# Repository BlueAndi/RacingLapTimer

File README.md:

# Racing Lap Timer
A racing lap timer, based on a laser sensor.

- [Racing Lap Timer](#racing-lap-timer)
- [Motivation](#motivation)
- [Initial Startup](#initial-startup)
- [Electronic](#electronic)
  - [Schematic](#schematic)
- [Software](#software)
  - [Preparation](#preparation)
  - [IDE](#ide)
  - [Installation](#installation)
  - [Build Project](#build-project)
  - [Update of the device](#update-of-the-device)
    - [Update via usb](#update-via-usb)
  - [Used Libraries](#used-libraries)
  - [System Context](#system-context)
- [Issues, Ideas And Bugs](#issues-ideas-and-bugs)
- [License](#license)
  - [Contribution](#contribution)

# Motivation
For line follower competitions a racing lap timer shall be used. It doesn't only measure the lap time, it shows it nice via web interface, inclusive automatically result table generation.

# Initial Startup
If the system starts up the first time, it will spawn a wifi access point with the SSID RacingLapTimer. Connect to it, it will request a password (default: "let me in").
Configure there the wifi network SSID/password to which the system shall later connect.

After configuration, the system will try to establish a connection. If the connection is not successful, the access point will be spawned again. Otherwise the credentials will be stored to persistent memory and loaded the next time automatically.

# Electronic

* [Wemos D1 Mini (esp8266)](https://docs.platformio.org/en/latest/boards/espressif8266/d1_mini.html)
* [Waveshare laser sensor](https://www.waveshare.com/wiki/Laser_Sensor)

## Schematic

Schematic files can be found [here](./doc/electronic/RacingLapTimer). These have been developed using KiCAD 6.

### MCU

- Digital signal of laser sensor is connected to D1/GPIO_5 of the Wemos D1 Mini.
- Power is supplied by USB 5V directly to the Wemos D1 Mini

### Laser Power Supply

- Laser module Vcc shall be 3.3V, because MCU is only 3.3V tolerant.
- THT or SMD resistor options are provided. **DO NOT PLACE ALL RESISTORS**.

### Laser Sensor

- Pin header for Waveshare Laser Sensor.

## PCB 
### v1.0

- It is recommended to give the Laser Sensor some kind of support in order to protect the pin header from breaking. The height of the support depends on the pin headers used.

# Software

## Preparation
Install the serial driver for the Wemos D1 Mini board. Find the latest drivers here: https://www.wemos.cc/en/latest/ch340_driver.html

## IDE
The [PlatformIO IDE](https://platformio.org/platformio-ide) is used for the development. Its build on top of Microsoft Visual Studio Code.

## Installation
1. Install [VSCode](https://code.visualstudio.com/).
2. Install PlatformIO IDE according to this [HowTo](https://platformio.org/install/ide?install=vscode).
3. Close and start VSCode again.
4. Recommended is to take a look to the [quick-start guide](https://docs.platformio.org/en/latest/ide/vscode.html#quick-start).

## Build Project
1. Load workspace in VSCode.
2. Change to PlatformIO toolbar.
3. _Project Tasks -> Build_ or via hotkey ctrl-alt-b

## Update of the device

### Update via usb
1. Connect the Wemos D1 Mini board to your PC via USB.
2. Build and upload the software via _Project Tasks -> Upload_.
3. Build and upload the filesystem via _Project Tasks -> Upload File System image_.

## Used Libraries
* [Arduino](https://github.com/esp8266/Arduino) - ESP framework.
* [WifiManager](https://github.com/tzapu/WiFiManager) - ESP8266 WiFi Connection manager with fallback web configuration portal.
* [WebSockets](https://github.com/Links2004/arduinoWebSockets) - A WebSocket Server and Client for Arduino based on RFC6455.

## System Context

# Issues, Ideas And Bugs
If you have further ideas or you found some bugs, great! Create a [issue](https://github.com/BlueAndi/RacingLapTimer/issues) or if you are able and willing to fix it by yourself, clone the repository and create a pull request.

# License
The whole source code is published under the [MIT license](http://choosealicense.com/licenses/mit/).

## Contribution
Unless you explicitly state otherwise, any contribution intentionally submitted for inclusion in the work by you, shall be licensed as above, without any
additional terms or conditions.

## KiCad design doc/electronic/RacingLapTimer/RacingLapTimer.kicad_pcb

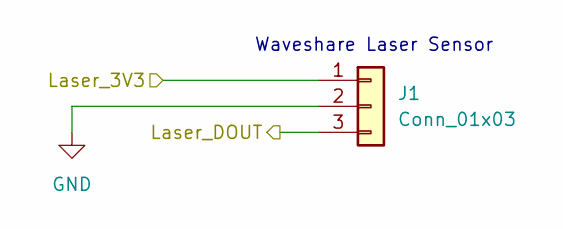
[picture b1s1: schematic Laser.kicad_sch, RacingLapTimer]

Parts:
J1: Conn_01x03; PinHeader_1x03_P2.54mm_Vertical

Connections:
/Laser/Laser_3V3: J1.1; also elsewhere on the board
/Laser/Laser_DOUT: J1.3; also elsewhere on the board
GND: J1.2; also elsewhere on the board

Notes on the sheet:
Waveshare Laser Sensor

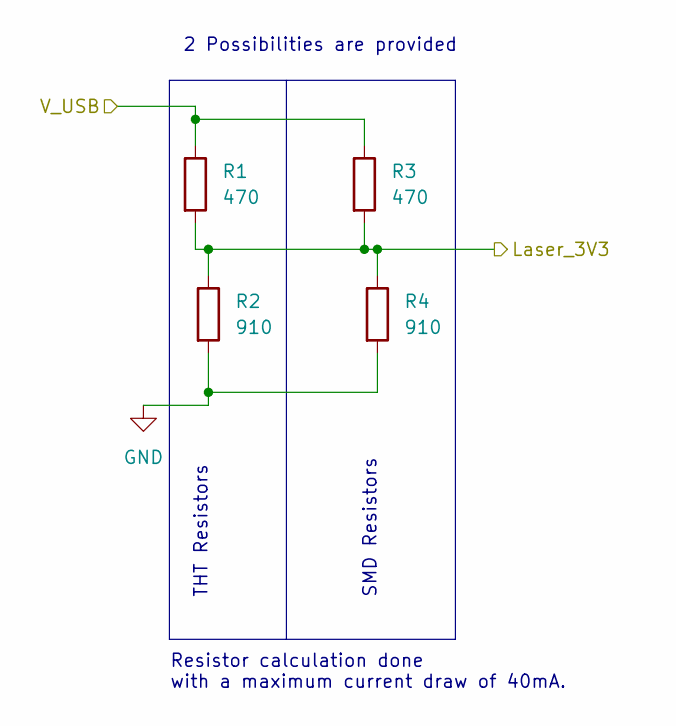
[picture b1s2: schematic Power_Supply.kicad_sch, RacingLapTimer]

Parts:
R1: 470; R_Axial_DIN0411_L9.9mm_D3.6mm_P15.24mm_Horizontal
R2: 910; R_Axial_DIN0411_L9.9mm_D3.6mm_P15.24mm_Horizontal
R3: 470; R_1206_3216Metric
R4: 910; R_1206_3216Metric

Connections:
/Laser/Laser_3V3: R1.2, R2.1, R3.2, R4.1; also elsewhere on the board
/MCU/V_USB: R1.1, R3.1; also elsewhere on the board
GND: R2.2, R4.2; also elsewhere on the board

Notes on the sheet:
SMD Resistors
2 Possibilities are provided
THT Resistors
Resistor calculation done with a maximum current draw of 40mA.

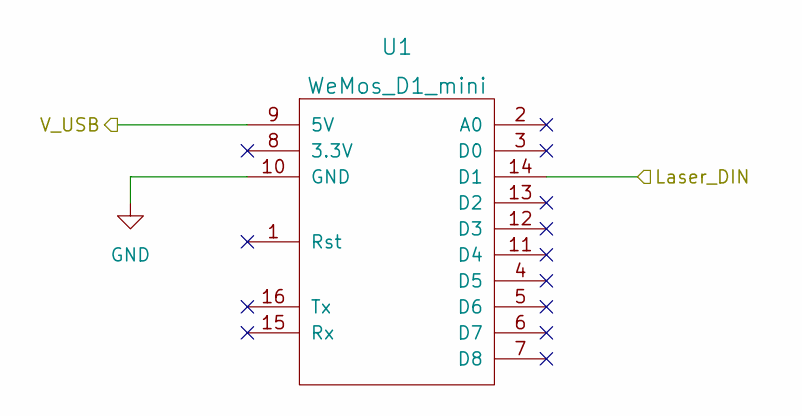
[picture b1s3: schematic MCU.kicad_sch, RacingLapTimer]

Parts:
U1: WeMos_D1_mini; wemos-d1-mini-with-pin-header-and-connector

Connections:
/Laser/Laser_DOUT: U1.14 (D1); also elsewhere on the board
/MCU/V_USB: U1.9 (5V); also elsewhere on the board
GND: U1.10 (GND); also elsewhere on the board

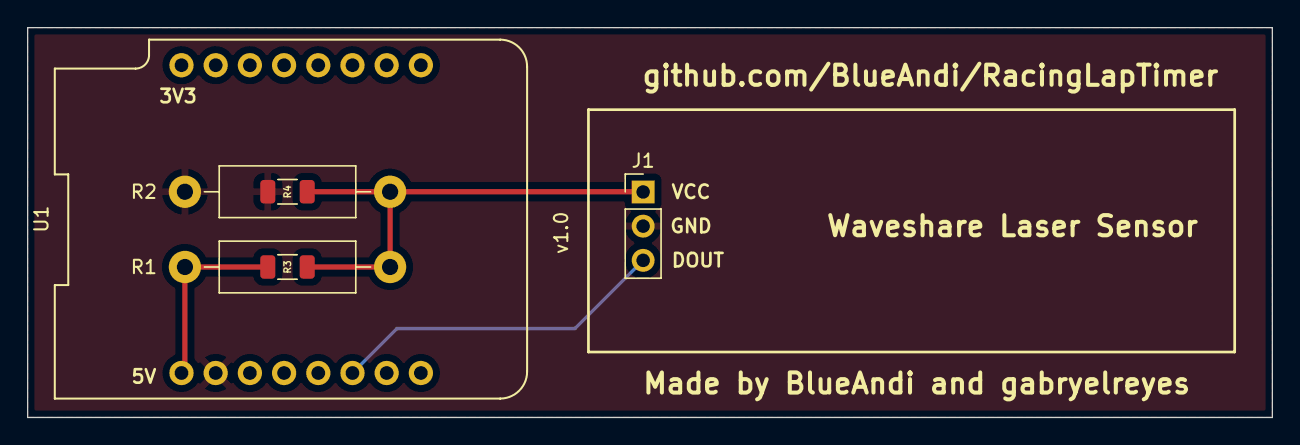
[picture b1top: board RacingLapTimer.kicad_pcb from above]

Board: 2 copper layers, 92.5 x 29.0 mm, 6 parts (0 on the bottom side), 4 nets.

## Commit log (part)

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2020-07-13 Initial commit.
2020-07-13 Library dependency manager configuration removed.
2020-07-13 Project title fixed in web interface.
2020-07-13 Cloned code removed.
2020-07-13 Screenshot added.
2020-07-13 Link to laser module fixed.
2020-07-13 Website cache increased to 1 day.
2020-07-13 WiFi manager requests now a password. Additional the error handling in the setup phase improved.
2020-07-13 Comment fixed.
2020-07-13 Initial startup description added.
2020-07-13 TOC updated.
2020-07-14 TODO regarding electronic schematic added.
2020-07-24 System context diagram added.
2020-07-25 System context diagram updated.
2020-09-08 3d housing models added
2020-11-07 VSCode workspace file removed.
2021-02-10 Changed WiFiMgr for WiFi soft Ap
2021-02-10 Fixed nullptr in JS
2021-02-22 Implemented Board namespace
2021-02-22 Implemented WLAN Class
2021-02-22 Implemented Web Server Class
2021-02-22 Added WLAN Class description
2021-02-22 Implemented Competition Class
2021-02-22 Changed Web Server name to prevent conflicts
2021-02-22 Deleted unused functions
2021-02-22 Added Missing Descriptions
2021-02-22 Added Error message
2021-02-22 Added wlan cycle to check connection. Added STA_AP Mode. Tested successfully on AP Mode
2021-02-22 Implemented STA and AP modes successfully
2021-02-23 Added Handle for POST method
2021-02-23 Added Configuration Webpage
2021-02-23 Initialize AP Mode when unable to connect to STA
2021-02-23 Fixed POST Argument Name
2021-02-23 Passed wlan instance to WebServer as argument. Implemented Credential handling from server to wlan settings
2021-02-23 Pseudo-implementation of Credential Saving
2021-02-23 Changed Arguments for constant references
2021-02-23 Moved Restart to WebServer
2021-02-23 Implemented Credential saving and importing.
2021-02-23 Changed Layout and Style of Config Page
2021-02-23 Travis configuration is obsolete and not planned to use.
2021-02-23 Doxygen configuration added.
2021-02-23 Doxygen input sources fixed.
2021-02-23 Initial use of CI
    Perform doxygen document generation.
2021-02-23 CI badge added and TOC updated.
2021-02-23 Update main.yml
    doxygen action version 1.2.3 used now.
2021-02-23 Update main.yml
    Debug CI commit
2021-02-23 Native platform added, mainly for static checks on CI.
2021-02-23 Update main.yml
    Checkout source step added.
2021-02-23 Update main.yml
    Perform static checks.
2021-02-23 Update main.yml
    Setup python and all platformio dependencies on CI.
2021-02-23 Update main.yml
    Platformio environment name fixed for performing static checks.
2021-02-23 git shall ignore generated doxygen documentation.
2021-02-23 Treat doxygen warnings as errors and check for parameter descriptions.
2021-02-24 Added MIT Licence
2021-02-24 Fixed and added Doxygen Comments
2021-02-24 Changed WLAN Class name for WIFI
2021-02-24 Initializaion of Credentials in Constructor
2021-02-24 Fixed comment after Class renaming
2021-02-24 Force check for undocumented stuff.
2021-02-24 Update main.yml
    Include Playground branch for push events.
2021-02-24 Static checks shall be done in src, lib and include folder.
2021-02-24 If cppcheck fails, it shall return 1 to force CI abort.
2021-02-24 The CI shall abort for any doxygen warning.
2021-02-24 Set bash script executable flag.
2021-02-26 WiFi Credentials defined in initialization list.
2021-02-26 Fixed Doxygen Documentation
2021-02-26 Added missing "static" Keyword for local methods
2021-02-26 Renamed WLAN Module into WIFI
2021-02-26 Added missing "static" Keyword for local members
2021-02-26 Added Sequence Diagram for Main Application
2021-03-01 Avoid checking files in, which are created automatically
    doxygen warnings file removed.
2021-03-03 Reverted 3rd Party file
2021-03-03 Fixed input, main and list tags
2021-03-03 Fixed nullptr assignment
2021-03-03 Updated Copyright Year 2020-2021
2021-03-03 Changed Header and structure layout of files
2021-03-03 Function Descriptions only on Header Files
2021-03-03 Renamed Boolean flags to improve readability
2021-03-03 Moved variables and constants to header. Declared as Class members
2021-03-03 Fixed Coding Style for WiFi Class
2021-03-03 Prevent copy or a assign a WIFI object
2021-03-03 Fixed Coding Style for Competition Class
2021-03-03 Implemented EEPROM abstraction into a new Class
2021-03-03 Removed Input parameter in class constructor
2021-03-03 Moved Initialization of File System to main.cpp
2021-03-03 Renamed runCycle method
2021-03-03 Changed Filename and preprocessor define to match class name
2021-03-03 Check the validity of Station credentials
2021-03-11 Moved static variables to class members. Unmounted Filesystem in Class Destructor.
2021-03-11 Added missing Doxygen description
2021-03-11 Ignore vscode folder
2021-03-11 Removed unused WiFiManager Library
2021-03-11 Simplified implementation of Credential management
2021-03-11 Fixed missing function call
2021-03-11 Fixed Coding Style
2021-03-11 Prevent copy and assignment of LapTriggerWebServer Instance
2021-03-11 Increased WiFi Timeout for STA Connection to 30 Seconds
2021-03-11 Fixed Bug: Invalid credentials are found after uploading code to Board
2021-03-12 Added missing Slash
2021-03-12 Added language tag
2021-03-12 Fixed Indentation
2021-03-12 Fixed File Description
2021-03-12 Fixed Coding Style and initialization of variables
2021-03-12 Added missing Static Keyword
2021-03-12 Removed Debugging printf
2021-03-12 Implemented method for retrieval of saved strings
2021-03-12 Cloned code replaced by function call. Replaced Magic Numbers for static constants.
2021-03-17 #5 Moved definition of constant to initialization list
2021-03-17 #6 Added misssing "static" Keyword
2021-03-17 #6 Fixed Coding Style on Class Members
2021-03-19 CI shall perform a compile check.
2021-03-19 Remove "unused function" check, because there is a bug in cppcheck, which causes false positives.
2021-03-20 Coding style: Module global variables start with a lowercase 'g'. MISRA: A if/else chain shall end with the a "else" to ensure nothing is forgotten.
2021-03-20 Only use doxygen style for members, variables, functions and methods.
2021-03-20 Unnecessary heap usage removed. Coding style violations fixed.
2021-03-20 Coding guideline violations. Not all member variables were initialized.
2021-03-20 Mounting the persistent memory shall be done in the startup initialization, not hidden somewhere in class. If later other classes must be access it too, it would be getting strange.
2021-03-26 #7 Renamed "Configuration" into "Settings"
2021-03-26 #7 Added "Number of Groups" to Competition and method to return its value
2021-03-26 #7 Added "GROUPS" to possible WS Command and responses
2021-03-26 #7 Added "Edit Groups" to Settings Page. Added Web socket Connection.
2021-03-26 #7 Added Method to request number of groups. Added "GROUPS" to possible WS Commands in Client Side.
2021-04-04 #7 Fetching Number Of Groups from permanent memory
2021-04-04 Implemented save and fetch of Integers from memory
2021-04-04 Renamed "GET_GROUPS" WS Command
2021-04-04 #7 Implemented "SAVE_GROUPS" WS Command
2021-04-04 #7 Implemented Parameter parsing from WS. Implemented SAVE_GROUPS Command
2021-04-04 #7 Result Table changes according to configured number of groups
2021-04-04 #7 Moved saving of number of groups. Save and get are done in Competition Class
2021-04-04 Set 10 as the maximum number of groups
2021-04-04 #8 Added Result Table to Competition Class
2021-04-04 #8 Save Group that has been Released by client
2021-04-04 #8 Client notifies Target which group is released
2021-04-04 #8 Update Result Table Arry with fastest runs
2021-04-04 #8 Implemented GET_TABLE WS Command
2021-04-04 Added second parameter to "FINISHED" WS event
2021-04-04 #8 Implementation for "GET_TABLE" WS Command
2021-04-16 #9 Changed name for consistency
2021-04-16 #9 Added missing Slash
2021-04-23 #9 Renamed function from "save" into "set" for convention
2021-04-23 #9 Fixed NVM Address name and Calculation
2021-04-23 #9 Fixed function names to "get/set" convention
2021-04-23 #9 Added missing spaces
2021-04-23 #9 Parsing of WS Text event in separate method
2021-04-23 #9 Deleted const reference for intrinsic type
2021-04-23 #9 Changed formatting of output messages
2021-04-23 #9 Improved Method description
2021-04-30 #9 Fixed return descriptions
2021-04-30 #9 GetNumberOfGroups moved to Competition class.
2021-04-30 #9 setGroups moved to Competition Class
2021-04-30 #9 Fixed old link to webpage
2021-04-30 #9 Fixed const and reference parameters
2021-04-30 #9 Fixed missing initialization of local variables
2021-04-30 #9 WS Payload casted as char
2021-04-30 #9 Check for empty parameter
2021-04-30 #9 Separation of group-setup functions.
2021-04-30 Contribution info added.
2021-04-30 #9 Fixed Parameter Description
2021-04-30 #9 Added missing brackets
2021-04-30 #9 Improved performance casting on local variable
2021-04-30 #9 processTime function separated from onEvent
2021-04-30 #9 Re-Implemented getSavedTable()
2021-04-30 #9 Group-setup Functions after WS Connection
2021-05-21 #9 Promises for setup functions
2021-05-21 #9 Fixed inconsistence in variable type
2021-05-21 #9 Fixed Return of getLaptime
2021-05-21 #9 Removed unnecessary const references
2021-05-21 #9 Added missing initializer
2021-05-21 #9 Fixed check for undefined
2021-05-28 #10 Created "Clear Laptime" Buttons
2021-05-28 #10 Implemented CLEAR Command
2021-05-28 #10 Implemented clearLaptime Method
2021-05-28 #10 Implemented clearAll Method
2021-06-18 #11 Fixed bug after Websocket Library update
2021-06-25 Added Exception Decoder to PIO Monitor
2021-06-25 Integration of Test Code
2021-07-15 Use the logging module for log output on the serial interface.
2021-07-16 Log output improved for easier reading.
2021-07-16 Formal stuff in the headers fixed.
2021-07-16 Line feed removed from some log outputs and log header adapted to longest filename.
2021-07-28 Created groupConfig Webpage
2021-07-28 Moved "Number of Groups" to GroupConfig webpage
2021-07-28 Added Settings table dependent of number of groups
2021-07-28 Deleted unused function
2021-07-28 Implemented SET_NAME Command
2021-07-28 Implemented dummy function for testing SET_NAME
2021-08-06 Implemented set and get functions for group name
2021-08-06 Implementation of SET_NAME cmd
2021-08-20 Changed Param delimiter to ":"
2021-08-20 GET_NAME Command implemented
2021-08-20 Implemented CLEAR_NAME Command
2021-11-13 Moved CLEAR ALL button from settings to G.Config
2021-11-13 "Accept Run" button implemented. Functionality not implemented on server
2021-11-13 Implemented accept and reject buttons
2021-11-13 Group names shown in Table and buttons
2021-11-14 Implemented reject run in server
2021-11-16 Fix Doxygen error
2022-01-20 Variables moved to the right position.
2022-01-20 A group/team extracted to a separate class.
2022-01-20 Use WiFi instead of WLAN.
2022-01-20 The EEPROM address data type shall consider the max. EEPROM size of 512 bytes.
2022-01-20 Settings and generic EEPROM access functions divided. Additional the group name is now stored in the settings too.
2022-01-21 Variable scope reduced.
2022-01-21 If a group name is empty, the name which to show in the web interface will be handled now in the web interface itself.
2022-02-17 Housing V2
2022-11-11 Initial Commit of PCB Project. Uses KiCAD 6
2022-11-11 Added Wemos D1 Mini Library
2022-11-11 PCB Version 1.0
2022-11-11 Moved electronic-related documents to electronics folder
2022-11-11 Fixed Missing annotations on silk layer
2022-11-11 Added Image of PCB
2022-11-11 Added Pictures of schematic files v1.0
2022-11-17 Leg Extensors added Increase the height of the barrier for use with bigger models
2023-01-19 Copyright year updated
2023-01-19 Platform and libs now with versions.
2023-01-20 Workflow actions updated to latest version.
2023-03-26 Platforms updated, static check configuration separated, number of static checks extended.
2023-09-18 Static check shall fail in case of medium or high priority errors.
2023-09-18 Platform and libs updated.
2023-09-18 Use const pointer if possible to avoid static check error.
2023-09-19 Removed non-standard exitcode of cppcheck
2023-09-19 Suppressed constParameterPointer defect. Defect comes from WebSocket library
2024-01-03 Copyright year updated.

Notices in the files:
README.md:
License: MIT
